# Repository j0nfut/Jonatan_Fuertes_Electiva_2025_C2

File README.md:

# Jonatan_Fuertes_Electiva_2025_C2
Repocitorio de electiva

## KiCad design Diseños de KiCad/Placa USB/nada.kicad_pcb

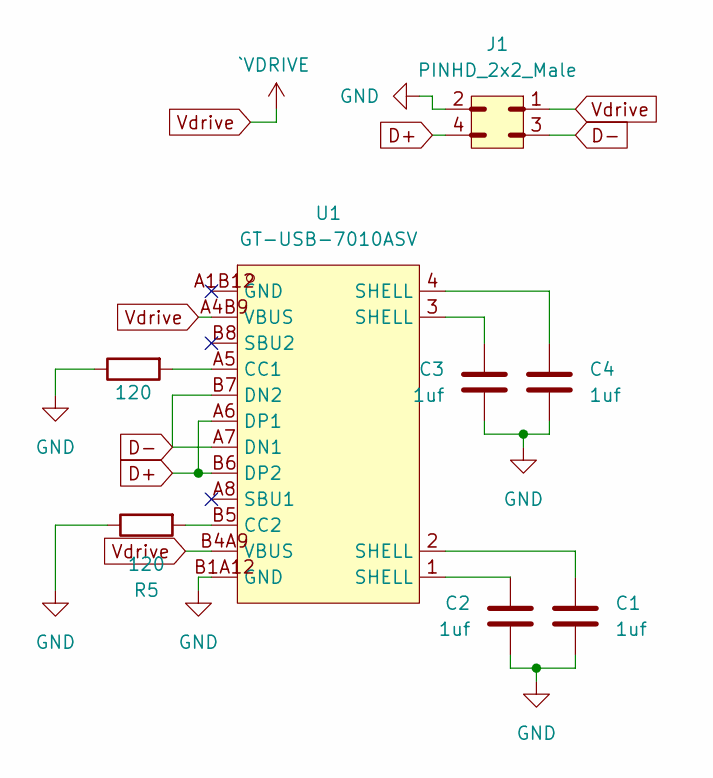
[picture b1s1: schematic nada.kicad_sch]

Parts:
C1, C2, C3, C4: 1uf; C_0603_1608Metric
J1: PINHD_2x2_Male; PinHeader_2x02_P2.54mm_Horizontal
R1, R5: 120; R_0603_1608Metric
U1: GT-USB-7010ASV; USB-C-SMDpersonalizado; LCSC Part C2988369

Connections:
D+: J1.4, U1.A6 (DP1), U1.B6 (DP2)
D-: J1.3, U1.A7 (DN1), U1.B7 (DN2)
GND: C1.2, C2.1, C3.1, C4.1, J1.2, R1.1, R5.1, U1.B1A12 (GND)
unnamed: C1.1, U1.2 (SHELL)
unnamed: C2.2, U1.1 (SHELL)
unnamed: C3.2, U1.3 (SHELL)
unnamed: C4.2, U1.4 (SHELL)
unnamed: R1.2, U1.A5 (CC1)
unnamed: R5.2, U1.B5 (CC2)
Vdrive: J1.1, U1.A4B9 (VBUS), U1.B4A9 (VBUS)

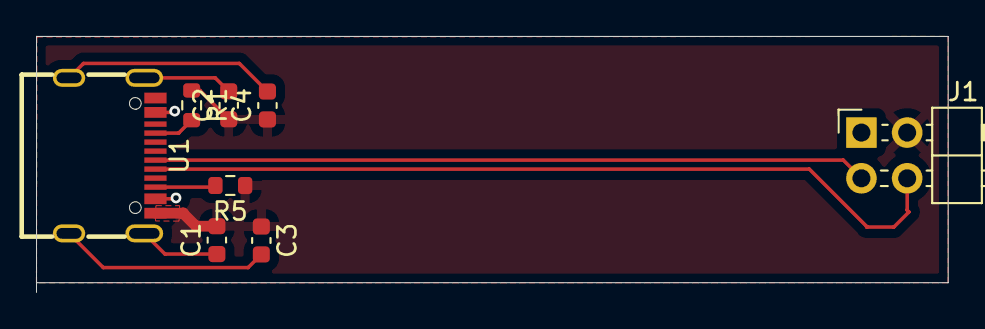
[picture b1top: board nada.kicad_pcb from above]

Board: 2 copper layers, 50.7 x 14.2 mm, 8 parts (0 on the bottom side), 10 nets.

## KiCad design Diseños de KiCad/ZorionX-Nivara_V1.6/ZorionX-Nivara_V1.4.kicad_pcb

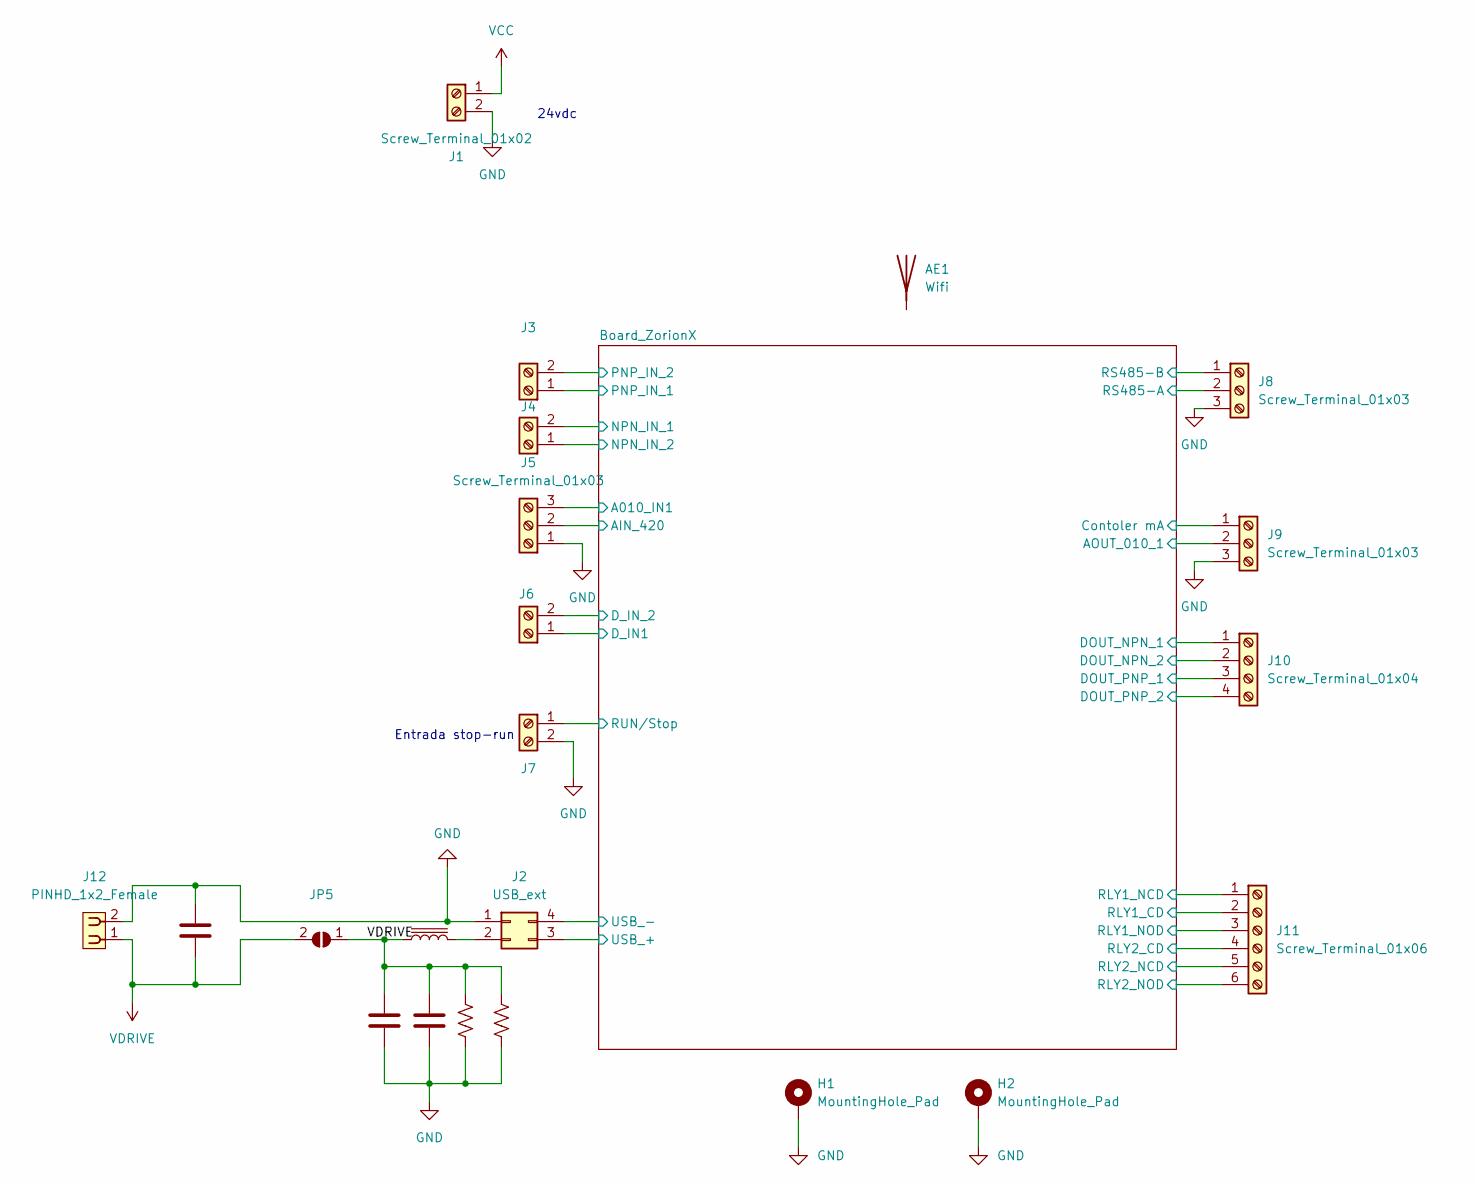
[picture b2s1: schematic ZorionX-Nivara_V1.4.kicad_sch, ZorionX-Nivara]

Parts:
AE1: Wifi
C18, C19, C20: 1uf; C_0603_1608Metric
H1, H2: MountingHole_Pad; MountingHole_3.2mm_M3_Pad_Via
J1, J3, J4, J6, J7: Screw_Terminal_01x02; TerminalBlock_Phoenix_PT-1,5-2-5.0-H_1x02_P5.00mm_Horizontal
J2: USB_ext; PinSocket_2x02_P2.54mm_Vertical
J5, J8, J9: Screw_Terminal_01x03; TerminalBlock_Phoenix_PT-1,5-3-3.5-H_1x03_P3.50mm_Horizontal
J10: Screw_Terminal_01x04; TerminalBlock_Phoenix_PT-1,5-4-5.0-H_1x04_P5.00mm_Horizontal
J11: Screw_Terminal_01x06; TerminalBlock_Phoenix_PT-1,5-6-5.0-H_1x06_P5.00mm_Horizontal
J12: PINHD_1x2_Female; PinSocket_1x02_P2.54mm_Vertical
JP5: SolderJumper_2_Open; SolderJumper-2_P1.3mm_Open_RoundedPad1.0x1.5mm
L2: L_Iron; L_Bourns-SRN6028
R25, R39: R_US; R_0603_1608Metric

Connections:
4_20v_mA: J5.2; also elsewhere on the board
/Board_ZorionX/A010_IN1: J5.3; also elsewhere on the board
/Board_ZorionX/AOUT_010_1: J9.2; also elsewhere on the board
/Board_ZorionX/Contoler mA: J9.1; also elsewhere on the board
/Board_ZorionX/DOUT_NPN_1: J10.1; also elsewhere on the board
/Board_ZorionX/DOUT_NPN_2: J10.2; also elsewhere on the board
/Board_ZorionX/DOUT_PNP_1: J10.3; also elsewhere on the board
/Board_ZorionX/DOUT_PNP_2: J10.4; also elsewhere on the board
/Board_ZorionX/D_IN1: J6.1; also elsewhere on the board
/Board_ZorionX/D_IN_2: J6.2; also elsewhere on the board
/Board_ZorionX/NPN_IN_1: J4.2; also elsewhere on the board
/Board_ZorionX/NPN_IN_2: J4.1; also elsewhere on the board
/Board_ZorionX/PNP_IN_1: J3.1; also elsewhere on the board
/Board_ZorionX/PNP_IN_2: J3.2; also elsewhere on the board
/Board_ZorionX/RLY1_CD: J11.2; also elsewhere on the board
/Board_ZorionX/RLY1_NCD: J11.1; also elsewhere on the board
/Board_ZorionX/RLY1_NOD: J11.3; also elsewhere on the board
/Board_ZorionX/RLY2_CD: J11.4; also elsewhere on the board
/Board_ZorionX/RLY2_NCD: J11.5; also elsewhere on the board
/Board_ZorionX/RLY2_NOD: J11.6; also elsewhere on the board
/Board_ZorionX/RS485-A: J8.2; also elsewhere on the board
/Board_ZorionX/RS485-B: J8.1; also elsewhere on the board
/Board_ZorionX/USB_+: J2.3; also elsewhere on the board
/Board_ZorionX/USB_-: J2.4; also elsewhere on the board
/RUN/Stop: J7.1
GND: C18.2, C19.2, C20.1, H1.1, H2.1, J1.2, J2.1, J5.1, J7.2, J8.3, J9.3, J12.2, R25.2, R39.2; also elsewhere on the board
unnamed: J2.2, L2.2
VCC: J1.1; also elsewhere on the board
VDRIVE: C18.1, C19.1, C20.2, J12.1, JP5.1 (A), JP5.2 (B), L2.1, R25.1, R39.1

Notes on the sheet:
24vdc
Entrada stop-run

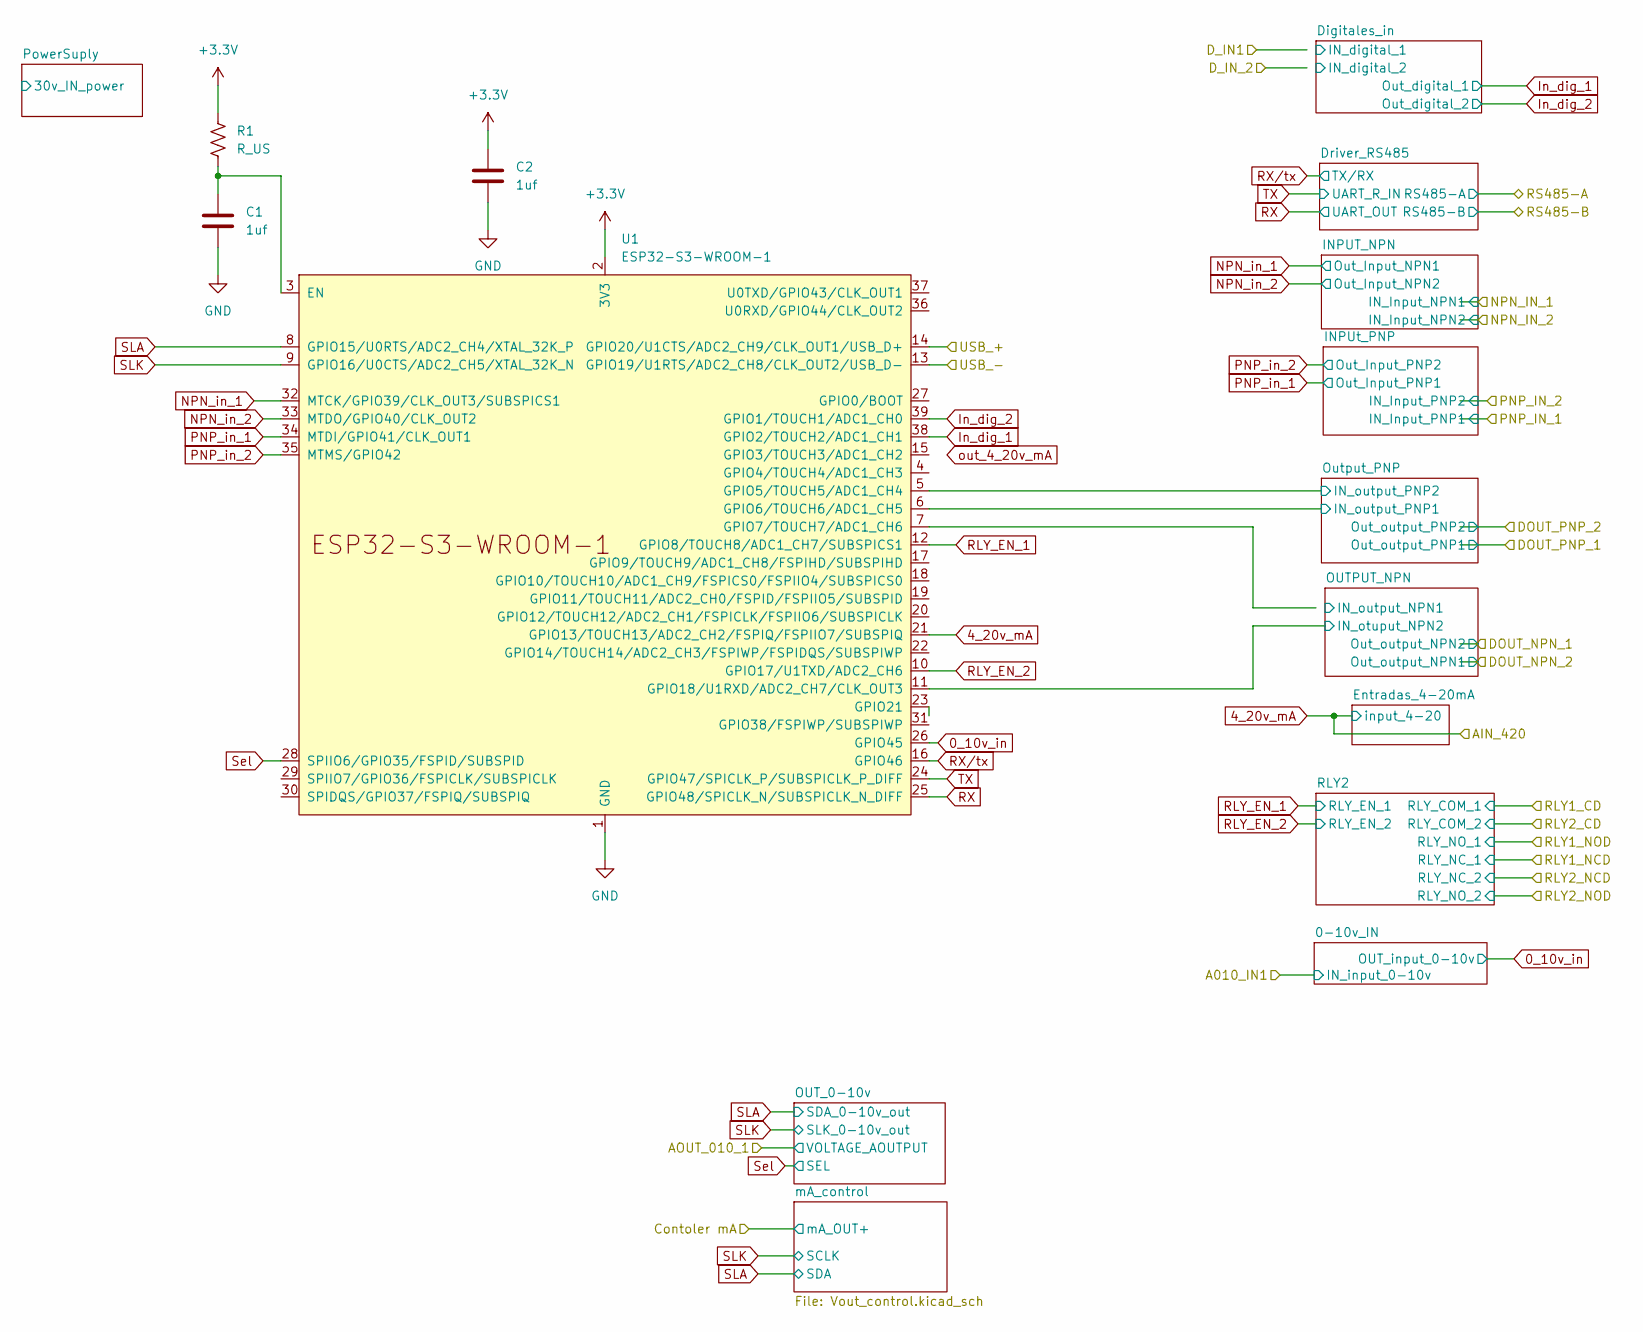
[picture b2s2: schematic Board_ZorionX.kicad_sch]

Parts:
C1, C2: 1uf; C_0603_1608Metric
R1: R_US; R_0603_1608Metric
U1: ESP32-S3-WROOM-1

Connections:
0_10v_in: U1.26 (GPIO45); also elsewhere on the board
4_20v_mA: U1.21 (GPIO13/TOUCH13/ADC2_CH2/FSPIQ/FSPIIO7/S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); also elsewhere on the board
+3.3V: C2.1, R1.1, U1.2 (3V3); also elsewhere on the board
/Board_ZorionX/OUTPUT_NPN/IN_otuput_NPN2: U1.11 (GPIO18/U1RXD/ADC2_CH7/CLK_OUT3); also elsewhere on the board
/Board_ZorionX/OUTPUT_NPN/IN_output_NPN1: U1.7 (GPIO7/TOUCH7/ADC1_CH6); also elsewhere on the board
/Board_ZorionX/Output_PNP/IN_output_PNP1: U1.6 (GPIO6/TOUCH6/ADC1_CH5); also elsewhere on the board
/Board_ZorionX/Output_PNP/IN_output_PNP2: U1.5 (GPIO5/TOUCH5/ADC1_CH4); also elsewhere on the board
/Board_ZorionX/USB_+: U1.14 (GPIO20/U1CTS/ADC2_CH9/CLK_OUT1/USB_D+); also elsewhere on the board
/Board_ZorionX/USB_-: U1.13 (GPIO19/U1RTS/ADC2_CH8/CLK_OUT2/USB_D-); also elsewhere on the board
GND: C1.2, C2.2, U1.1 (GND), U1.40 (GND), U1.41 (GND); also elsewhere on the board
In_dig_1: U1.38 (GPIO2/TOUCH2/ADC1_CH1); also elsewhere on the board
In_dig_2: U1.39 (GPIO1/TOUCH1/ADC1_CH0); also elsewhere on the board
NPN_in_1: U1.32 (MTCK/GPIO39/CLK_OUT3/SUBSPICS1); also elsewhere on the board
NPN_in_2: U1.33 (MTDO/GPIO40/CLK_OUT2); also elsewhere on the board
unnamed: C1.1, R1.2, U1.3 (EN)
PNP_in_1: U1.34 (MTDI/GPIO41/CLK_OUT1); also elsewhere on the board
PNP_in_2: U1.35 (MTMS/GPIO42); also elsewhere on the board
RLY_EN_1: U1.12 (GPIO8/TOUCH8/ADC1_CH7/SUBSPICS1); also elsewhere on the board
RLY_EN_2: U1.10 (GPIO17/U1TXD/ADC2_CH6); also elsewhere on the board
RX: U1.25 (GPIO48/SPICLK_N/SUBSPICLK_N_DIFF); also elsewhere on the board
RX/tx: U1.16 (GPIO46); also elsewhere on the board
SLA: U1.8 (GPIO15/U0RTS/ADC2_CH4/XTAL_32K_P); also elsewhere on the board
SLK: U1.9 (GPIO16/U0CTS/ADC2_CH5/XTAL_32K_N); also elsewhere on the board
Sel: U1.28 (SPIIO6/GPIO35/FSPID/SUBSPID); also elsewhere on the board
TX: U1.24 (GPIO47/SPICLK_P/SUBSPICLK_P_DIFF); also elsewhere on the board

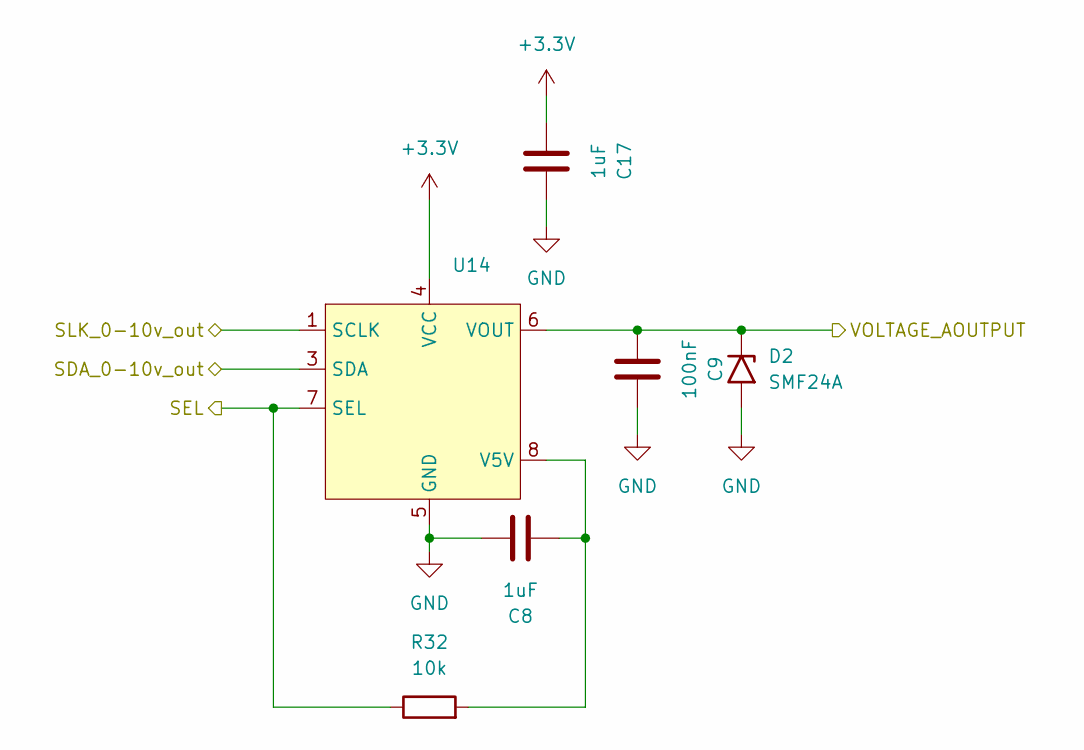
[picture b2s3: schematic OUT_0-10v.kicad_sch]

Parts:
C8, C17: 1uF; C_0603_1608Metric
C9: 100nF; C_0603_1608Metric
D2: SMF24A; D_SMF; LCSC# C7495269
R32: 10k; R_0603_1608Metric
U14: SOIC-8_5.3x6.2mm_P1.27mm

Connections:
+3.3V: C17.2, U14.4 (VCC); also elsewhere on the board
/Board_ZorionX/AOUT_010_1: C9.2, D2.1 (A1), U14.6 (VOUT); also elsewhere on the board
GND: C8.1, C9.1, C17.1, D2.2 (A2), U14.5 (GND); also elsewhere on the board
unnamed: C8.2, R32.2, U14.8 (V5V)
SLA: U14.3 (SDA); also elsewhere on the board
SLK: U14.1 (SCLK); also elsewhere on the board
Sel: R32.1, U14.7 (SEL); also elsewhere on the board

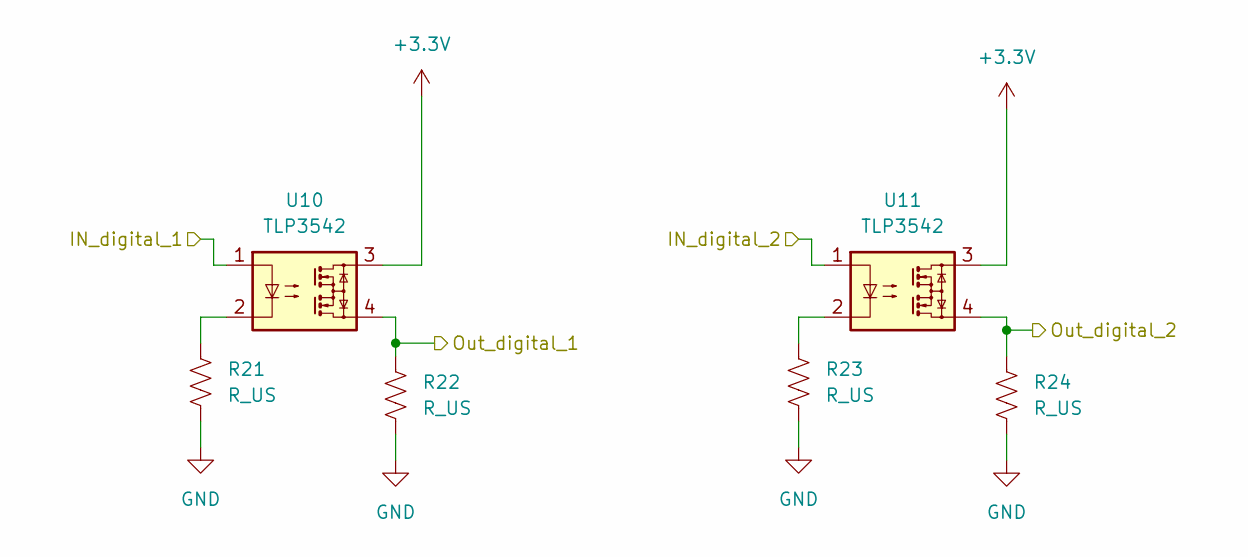
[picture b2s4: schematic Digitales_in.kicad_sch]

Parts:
R21, R22, R23, R24: R_US; R_0603_1608Metric
U10, U11: TLP3542; SOP-4_3.8x4.1mm_P2.54mm

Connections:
+3.3V: U10.3, U11.3; also elsewhere on the board
/Board_ZorionX/D_IN1: U10.1; also elsewhere on the board
/Board_ZorionX/D_IN_2: U11.1; also elsewhere on the board
GND: R21.2, R22.2, R23.2, R24.2; also elsewhere on the board
In_dig_1: R22.1, U10.4; also elsewhere on the board
In_dig_2: R24.1, U11.4; also elsewhere on the board
unnamed: R21.1, U10.2
unnamed: R23.1, U11.2

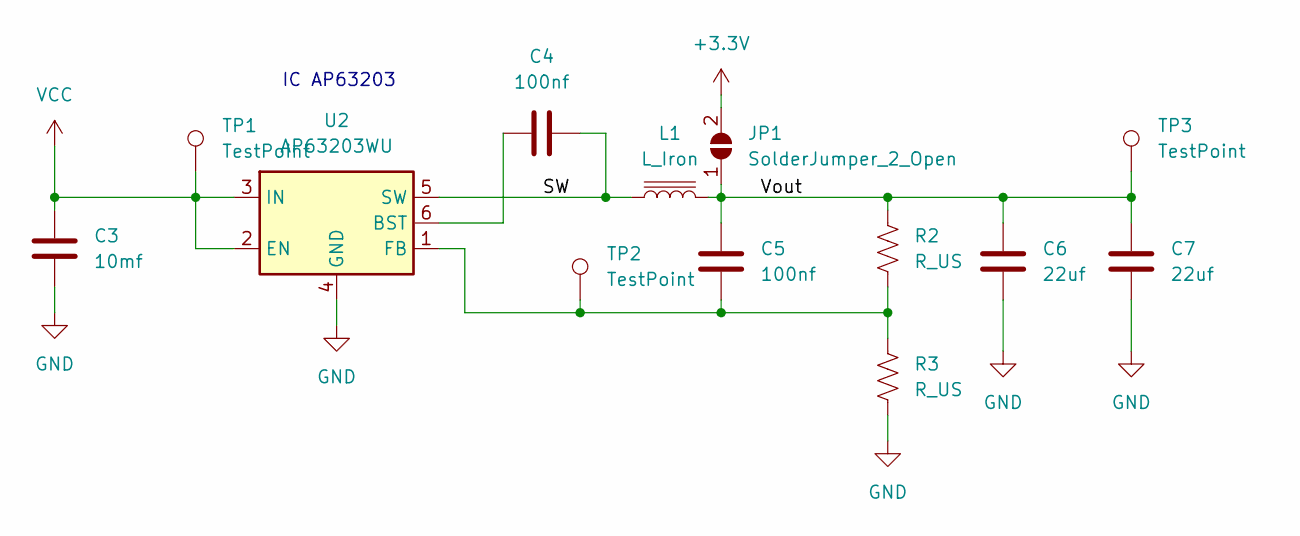
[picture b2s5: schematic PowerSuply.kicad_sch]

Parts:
C3: 10mf; C_1206_3216Metric
C4, C5: 100nf; C_0603_1608Metric
C6, C7: 22uf; C_0805_2012Metric
JP1: SolderJumper_2_Open; SolderJumper-2_P1.3mm_Open_RoundedPad1.0x1.5mm
L1: L_Iron; L_Bourns-SRN6028
R2, R3: R_US; R_0603_1608Metric
TP1, TP2, TP3: TestPoint; TestPoint_THTPad_1.0x1.0mm_Drill0.5mm
U2: AP63203WU; TSOT-23-6

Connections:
+3.3V: JP1.2 (B); also elsewhere on the board
/Board_ZorionX/PowerSuply/SW: C4.2, L1.1, U2.5 (SW)
/Board_ZorionX/PowerSuply/Vout: C5.1, C6.1, C7.1, JP1.1 (A), L1.2, R2.1, TP3.1
GND: C3.2, C6.2, C7.2, R3.2, U2.4 (GND); also elsewhere on the board
unnamed: C4.1, U2.6 (BST)
unnamed: C5.2, R2.2, R3.1, TP2.1, U2.1 (FB)
VCC: C3.1, TP1.1, U2.2 (EN), U2.3 (IN); also elsewhere on the board

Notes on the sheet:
IC AP63203

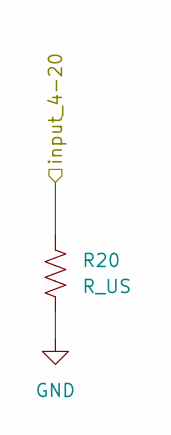
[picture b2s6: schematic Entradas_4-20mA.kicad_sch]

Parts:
R20: R_US; R_0603_1608Metric

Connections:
4_20v_mA: R20.1; also elsewhere on the board
GND: R20.2; also elsewhere on the board

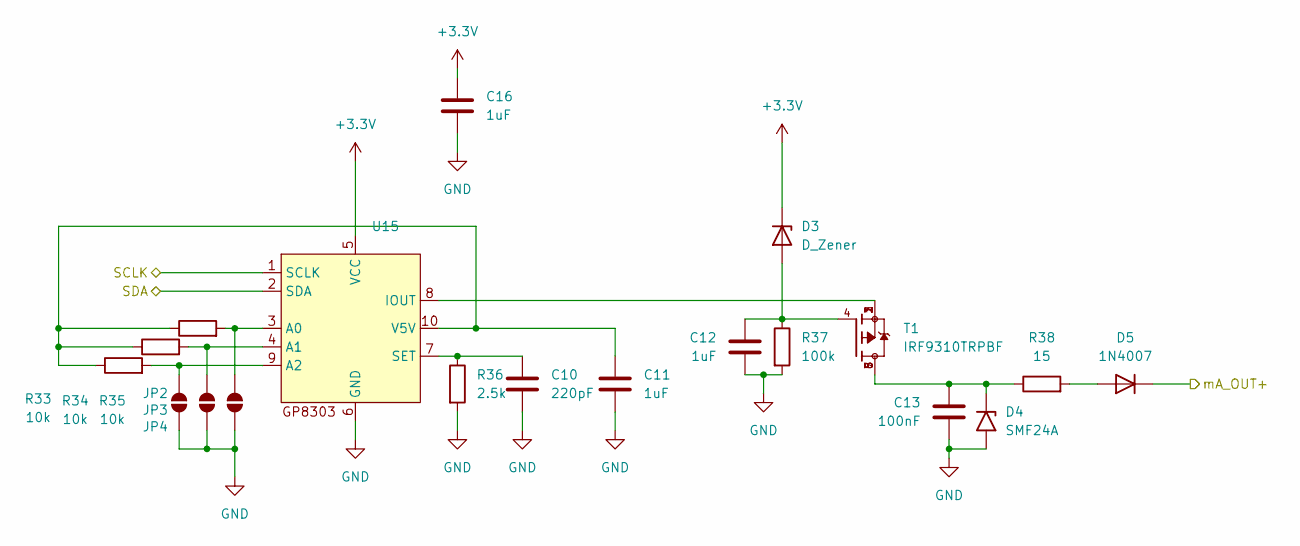
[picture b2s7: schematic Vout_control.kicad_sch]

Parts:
C10: 220pF; C_0603_1608Metric
C11, C12, C16: 1uF; C_0603_1608Metric
C13: 100nF; C_0603_1608Metric
D3: D_Zener; D_SMF
D4: SMF24A; D_SMF
D5: 1N4007; D_DO-41_SOD81_P10.16mm_Horizontal
JP2, JP3, JP4: SolderJumper_2_Open; SolderJumper-2_P1.3mm_Open_RoundedPad1.0x1.5mm
R33, R34, R35: 10k; R_0603_1608Metric
R36: 2.5k; R_0603_1608Metric
R37: 100k; R_0603_1608Metric
R38: 15; R_0603_1608Metric
T1: IRF9310TRPBF; SO-8_3.9x4.9mm_P1.27mm
U15: SSOP-10-1EP_3.9x4.9mm_P1mm_EP2.1x3.3mm

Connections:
+3.3V: C16.1, D3.1 (K), U15.5 (VCC); also elsewhere on the board
/Board_ZorionX/Contoler mA: D5.1 (K); also elsewhere on the board
GND: C10.2, C11.2, C12.2, C13.2, C16.2, D4.2 (A2), JP2.1 (A), JP3.1 (A), JP4.1 (A), R36.2, R37.2, U15.6 (GND); also elsewhere on the board
unnamed: C12.1, D3.2 (A), R37.1, T1.4
unnamed: C13.1, D4.1 (A1), R38.1, T1.5, T1.6, T1.7, T1.8
unnamed: D5.2 (A), R38.2
unnamed: JP2.2 (B), R33.2, U15.9 (A2)
unnamed: JP3.2 (B), R34.2, U15.4 (A1)
unnamed: JP4.2 (B), R35.2, U15.3 (A0)
unnamed: T1.1, T1.2, T1.3, U15.8 (IOUT)
unnamed: C10.1, R36.1, U15.7 (SET)
unnamed: C11.1, R33.1, R34.1, R35.1, U15.10 (V5V)
SLA: U15.2 (SDA); also elsewhere on the board
SLK: U15.1 (SCLK); also elsewhere on the board

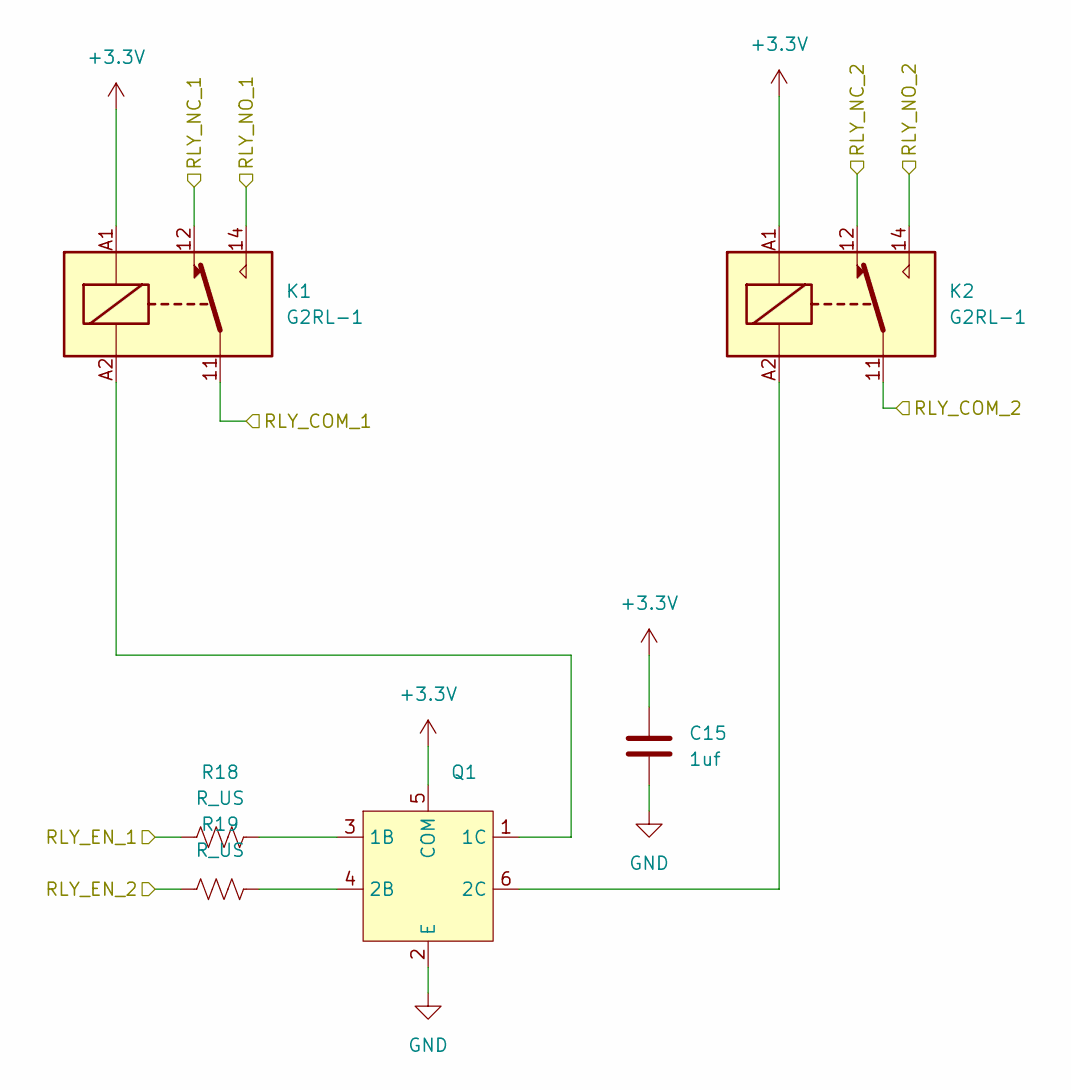
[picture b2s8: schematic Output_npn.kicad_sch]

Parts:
C15: 1uf; C_0603_1608Metric
K1, K2: G2RL-1; Relay_SPDT_Omron_G2RL-1
Q1: TSOT-23-6; LCSC# C2984831
R18, R19: R_US; R_0603_1608Metric

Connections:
+3.3V: C15.1, K1.A1, K2.A1, Q1.5 (COM); also elsewhere on the board
/Board_ZorionX/RLY1_CD: K1.11; also elsewhere on the board
/Board_ZorionX/RLY1_NCD: K1.12; also elsewhere on the board
/Board_ZorionX/RLY1_NOD: K1.14; also elsewhere on the board
/Board_ZorionX/RLY2_CD: K2.11; also elsewhere on the board
/Board_ZorionX/RLY2_NCD: K2.12; also elsewhere on the board
/Board_ZorionX/RLY2_NOD: K2.14; also elsewhere on the board
GND: C15.2, Q1.2 (E); also elsewhere on the board
unnamed: Q1.3 (1B), R18.2
unnamed: K1.A2, Q1.1 (1C)
unnamed: Q1.4 (2B), R19.2
unnamed: K2.A2, Q1.6 (2C)
RLY_EN_1: R18.1; also elsewhere on the board
RLY_EN_2: R19.1; also elsewhere on the board

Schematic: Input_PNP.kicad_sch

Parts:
R6, R7, R8, R9: R_US; R_0603_1608Metric
U4, U5: TLP3542; SOP-4_3.8x4.1mm_P2.54mm

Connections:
+3.3V: R7.1, R9.1; also elsewhere on the board
/Board_ZorionX/DOUT_NPN_1: R9.2, U5.3; also elsewhere on the board
/Board_ZorionX/DOUT_NPN_2: R7.2, U4.3; also elsewhere on the board
/Board_ZorionX/OUTPUT_NPN/IN_otuput_NPN2: U5.1; also elsewhere on the board
/Board_ZorionX/OUTPUT_NPN/IN_output_NPN1: U4.1; also elsewhere on the board
GND: R6.2, R8.2, U4.4, U5.4; also elsewhere on the board
unnamed: R6.1, U4.2
unnamed: R8.1, U5.2

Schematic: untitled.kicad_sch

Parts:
R26, R27, R28, R29: R_US; R_0603_1608Metric
U12, U13: TLP3542; SOP-4_3.8x4.1mm_P2.54mm

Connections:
+3.3V: R27.1, R29.1; also elsewhere on the board
/Board_ZorionX/NPN_IN_1: U12.1; also elsewhere on the board
/Board_ZorionX/NPN_IN_2: U13.1; also elsewhere on the board
GND: R26.2, R28.2, U12.4, U13.4; also elsewhere on the board
NPN_in_1: R27.2, U12.3; also elsewhere on the board
NPN_in_2: R29.2, U13.3; also elsewhere on the board
unnamed: R26.1, U12.2
unnamed: R28.1, U13.2

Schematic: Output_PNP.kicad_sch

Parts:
R10, R11, R12, R13: R_US; R_0603_1608Metric
U6, U7: TLP3542; SOP-4_3.8x4.1mm_P2.54mm

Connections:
+3.3V: U6.3, U7.3; also elsewhere on the board
/Board_ZorionX/DOUT_PNP_1: R11.1, U6.4; also elsewhere on the board
/Board_ZorionX/DOUT_PNP_2: R13.1, U7.4; also elsewhere on the board
/Board_ZorionX/Output_PNP/IN_output_PNP1: U6.1; also elsewhere on the board
/Board_ZorionX/Output_PNP/IN_output_PNP2: U7.1; also elsewhere on the board
GND: R10.2, R11.2, R12.2, R13.2; also elsewhere on the board
unnamed: R10.1, U6.2
unnamed: R12.1, U7.2

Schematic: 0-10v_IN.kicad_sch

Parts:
R30, R31: R_US; R_0603_1608Metric

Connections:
0_10v_in: R30.2, R31.1; also elsewhere on the board
/Board_ZorionX/A010_IN1: R30.1; also elsewhere on the board
GND: R31.2; also elsewhere on the board

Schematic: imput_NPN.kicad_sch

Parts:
R14, R15, R16, R17: R_US; R_0603_1608Metric
U8, U9: TLP3542; SOP-4_3.8x4.1mm_P2.54mm

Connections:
+3.3V: U8.3, U9.3; also elsewhere on the board
/Board_ZorionX/PNP_IN_1: U8.1; also elsewhere on the board
/Board_ZorionX/PNP_IN_2: U9.1; also elsewhere on the board
GND: R14.2, R15.2, R16.2, R17.2; also elsewhere on the board
unnamed: R14.1, U8.2
unnamed: R16.1, U9.2
PNP_in_1: R15.1, U8.4; also elsewhere on the board
PNP_in_2: R17.1, U9.4; also elsewhere on the board

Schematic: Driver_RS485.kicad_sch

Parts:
C14: 1uf; C_0603_1608Metric
D1: SM712_SOT23; SOT-23
R4, R5: 120; R_0603_1608Metric
U3: Rs_485

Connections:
+3.3V: C14.1, U3.1 (VCC); also elsewhere on the board
/Board_ZorionX/RS485-A: D1.1 (A1), R5.2; also elsewhere on the board
/Board_ZorionX/RS485-B: D1.2 (A2), R4.2; also elsewhere on the board
GND: C14.2, D1.3 (common), U3.2 (GND); also elsewhere on the board
unnamed: R5.1, U3.9 (A)
unnamed: R4.1, U3.8 (B)
RX: U3.4 (RXD); also elsewhere on the board
RX/tx: U3.5 (CON); also elsewhere on the board
TX: U3.3 (TXD); also elsewhere on the board

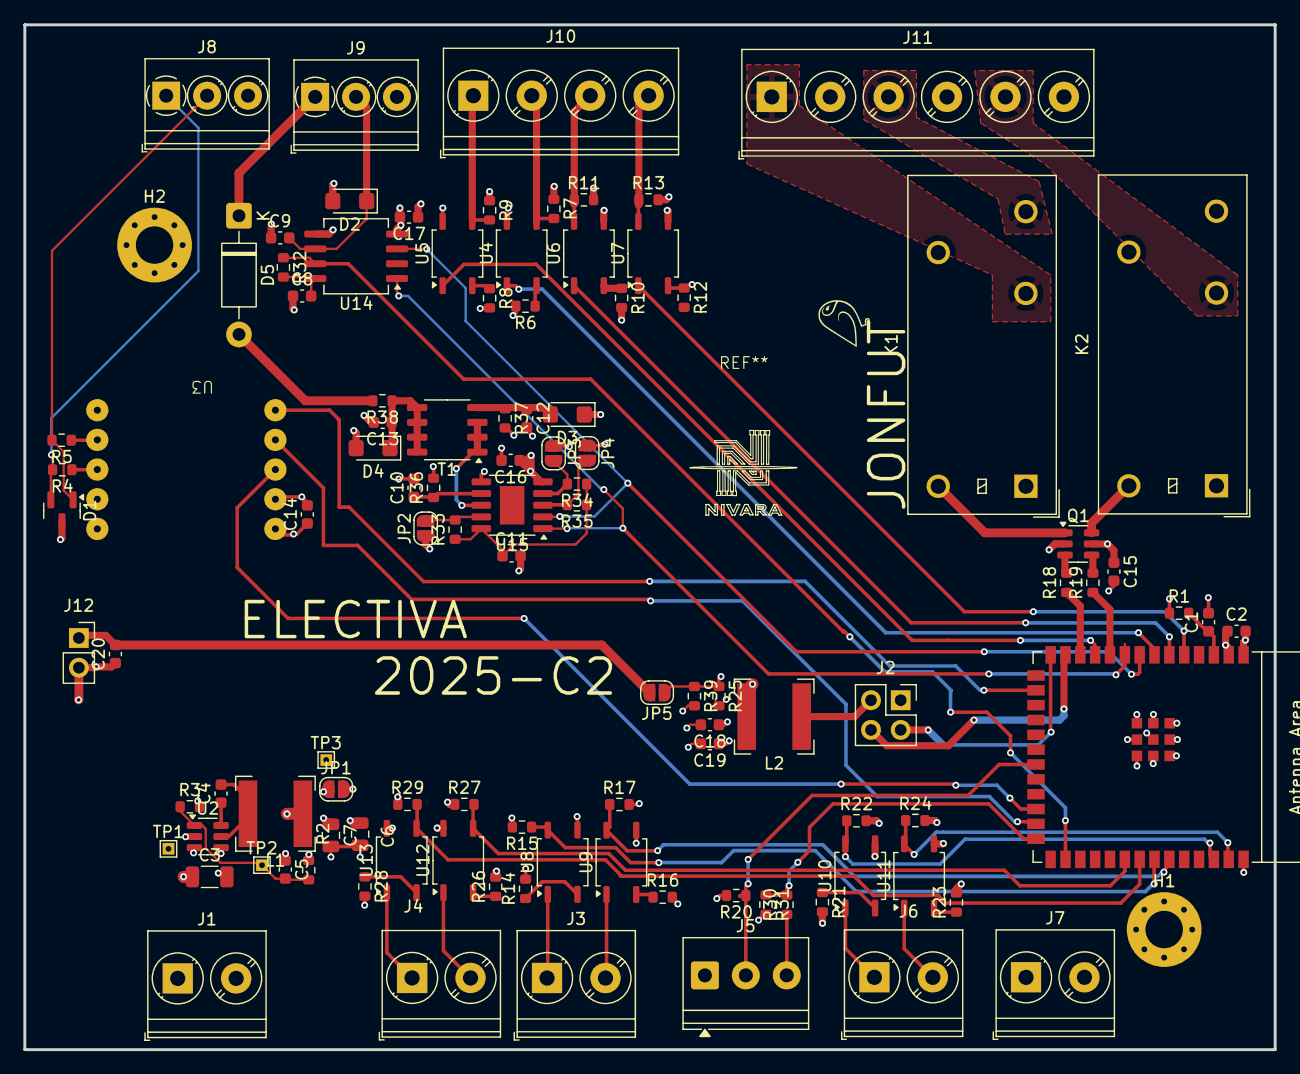
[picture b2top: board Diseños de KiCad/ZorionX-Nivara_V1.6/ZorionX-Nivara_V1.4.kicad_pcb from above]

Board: 4 copper layers, 107.0 x 87.7 mm, 107 parts (0 on the bottom side), 79 nets.

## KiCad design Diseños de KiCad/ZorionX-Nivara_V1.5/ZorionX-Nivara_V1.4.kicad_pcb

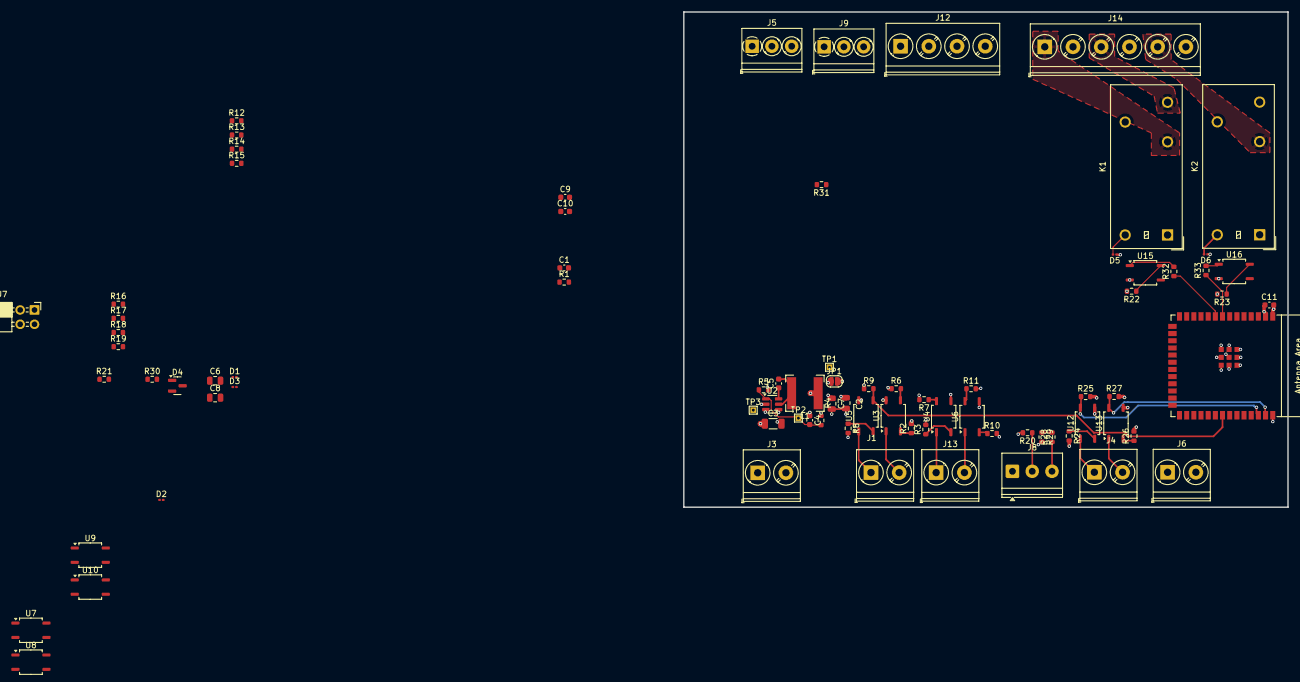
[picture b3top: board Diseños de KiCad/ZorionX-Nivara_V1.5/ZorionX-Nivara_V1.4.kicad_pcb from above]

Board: 4 copper layers, 107.0 x 87.7 mm, 82 parts (0 on the bottom side), 58 nets.

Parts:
C1, C9, C10, C11: 1uf; C_0603_1608Metric
C2, C7: 22uf; C_0805_2012Metric
C3: 10mf; C_1206_3216Metric
C4, C5: 100nf; C_0603_1608Metric
C6: 0.1uf; C_0805_2012Metric
C8: 1uf; C_0805_2012Metric
D1: D_Zener; L_0201_0603Metric
D2, D3, D5, D6: D; L_0201_0603Metric
D4: SM712_SOT23; SOT-23
J1, J3, J4, J6, J13: Screw_Terminal_01x02; TerminalBlock_Phoenix_PT-1,5-2-5.0-H_1x02_P5.00mm_Horizontal
J5, J8, J9: Screw_Terminal_01x03; TerminalBlock_Phoenix_PT-1,5-3-3.5-H_1x03_P3.50mm_Horizontal
J7: USB_ext; PinSocket_2x02_P2.54mm_Horizontal
J12: Screw_Terminal_01x04; TerminalBlock_Phoenix_PT-1,5-4-5.0-H_1x04_P5.00mm_Horizontal
J14: Screw_Terminal_01x06; TerminalBlock_Phoenix_PT-1,5-6-5.0-H_1x06_P5.00mm_Horizontal
JP1: SolderJumper_2_Open; SolderJumper-2_P1.3mm_Open_RoundedPad1.0x1.5mm
K1, K2: G2RL-1; Relay_SPDT_Omron_G2RL-1
L1: L_Iron; L_Bourns-SRN6028
R1, R2, R3, R4, R5, R6, R7, R8, R9, R10, R11, R12, R13, R14, R15, R16, R17, R18, R19, R20, R21, R22, R23, R24, R25, R26, R27, R28, R29, R30, R31, R32, R33: R_US; R_0603_1608Metric
TP1, TP2, TP3: TestPoint; TestPoint_THTPad_1.0x1.0mm_Drill0.5mm
U1: ESP32-S3-WROOM-1
U2: AP63203WU; TSOT-23-6
U3, U4, U5, U6, U7, U8, U9, U10, U12, U13, U15, U16: TLP3542; SOP-4_3.8x4.1mm_P2.54mm

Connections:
0_10v_in: R28.2, R29.1
4_20v_mA: J8.2, R20.1
+3.3V: C9.2, C10.2, C11.1, D2.1 (K), D5.1 (K), D6.1 (K), J12.1, J12.2, JP1.2 (B), K1.A1, K2.A1, R1.1, R6.1, R9.1, R17.1, R19.1, U1.2 (3V3), U4.3, U6.3, U7.3, U8.3, U12.3, U13.3
/Board_ZorionX/AOUT_010_1: C6.1, D1.1 (K), D2.2 (A), D3.1 (K), J9.2
/Board_ZorionX/DOUT_PNP_1: J12.3, R13.1, U7.4
/Board_ZorionX/DOUT_PNP_2: J12.4, R15.1, U8.4
/Board_ZorionX/D_IN1: J4.1, U12.1
/Board_ZorionX/D_IN_2: J4.2, U13.1
/Board_ZorionX/INPUt_PNP/Out_Input_PNP1: R7.1, U4.4
/Board_ZorionX/INPUt_PNP/Out_Input_PNP2: R11.1, U6.4
/Board_ZorionX/NPN_IN_2: J1.1, U5.1
/Board_ZorionX/OUTPUT_NPN/IN_otuput_NPN2: U1.11 (GPIO18/U1RXD/ADC2_CH7/CLK_OUT3), U10.1
/Board_ZorionX/OUTPUT_NPN/IN_output_NPN1: U1.7 (GPIO7/TOUCH7/ADC1_CH6), U9.1
/Board_ZorionX/Output_PNP/IN_output_PNP1: U1.6 (GPIO6/TOUCH6/ADC1_CH5), U7.1
/Board_ZorionX/Output_PNP/IN_output_PNP2: U1.5 (GPIO5/TOUCH5/ADC1_CH4), U8.1
/Board_ZorionX/PNP_IN_2: J13.1, U4.1
/Board_ZorionX/PowerSuply/SW: C5.2, L1.1, U2.5 (SW)
/Board_ZorionX/PowerSuply/Vout: C2.1, C4.1, C7.1, JP1.1 (A), L1.2, R4.1, TP1.1
/Board_ZorionX/RLY1_CD: J14.2, K1.11
/Board_ZorionX/RLY1_NCD: J14.1, K1.12
/Board_ZorionX/RLY1_NOD: J14.3, K1.14
/Board_ZorionX/RLY2_CD: J14.4, K2.11
/Board_ZorionX/RLY2_NCD: J14.5, K2.12
/Board_ZorionX/RLY2_NOD: J14.6, K2.14
/Board_ZorionX/RS485-A: D4.1 (A1), J5.2, R30.2
/Board_ZorionX/RS485-B: D4.2 (A2), J5.1, R31.2
/Board_ZorionX/USB_+: J7.4, U1.14 (GPIO20/U1CTS/ADC2_CH9/CLK_OUT1/USB_D+)
/Board_ZorionX/USB_-: J7.3, U1.13 (GPIO19/U1RTS/ADC2_CH8/CLK_OUT2/USB_D-)
GND: C1.2, C2.2, C3.2, C6.2, C7.2, C8.2, C11.2, D1.2 (A), D3.2 (A), D4.3 (common), J3.2, J5.3, J6.2, J7.2, J8.1, J9.3, R2.2, R3.2, R5.2, R7.2, R8.2, R10.2, R11.2, R12.2, R13.2, R14.2, R15.2, R16.2, R18.2, R20.2, R21.2, R22.2, R23.2, R24.2, R25.2, R26.2, R27.2, R29.2, U1.1 (GND), U1.40 (GND), U1.41 (GND), U2.4 (GND), U3.4, U5.4, U9.4, U10.4, U15.2, U16.2
In_dig_1: R25.1, U1.38 (GPIO2/TOUCH2/ADC1_CH1), U12.4
In_dig_2: R27.1, U1.39 (GPIO1/TOUCH1/ADC1_CH0), U13.4
NPN_in_1: J1.2, R6.2, U1.32 (MTCK/GPIO39/CLK_OUT3/SUBSPICS1), U3.1, U3.3
NPN_in_2: R9.2, U1.33 (MTDO/GPIO40/CLK_OUT2), U5.3
unnamed: D5.2 (A), K1.A2
unnamed: D6.2 (A), K2.A2
unnamed: R2.1, U3.2
unnamed: R3.1, U4.2
unnamed: R8.1, U5.2
unnamed: R10.1, U6.2
unnamed: R12.1, U7.2
unnamed: R14.1, U8.2
unnamed: R16.1, U9.2
unnamed: R17.2, U9.3
unnamed: R18.1, U10.2
unnamed: R19.2, U10.3
unnamed: R22.1, U15.4
unnamed: R23.1, U16.4
unnamed: R24.1, U12.2
unnamed: R26.1, U13.2
unnamed: R32.2, U15.1
unnamed: R33.2, U16.1
unnamed: C1.1, R1.2, U1.3 (EN)
unnamed: C5.1, U2.6 (BST)
unnamed: C4.2, R4.2, R5.1, TP2.1, U2.1 (FB)
PNP_in_1: J13.2, U1.34 (MTDI/GPIO41/CLK_OUT1), U1.35 (MTMS/GPIO42), U6.1
RLY_EN_1: R33.1, U1.8 (GPIO15/U0RTS/ADC2_CH4/XTAL_32K_P)
RLY_EN_2: R32.1, U1.9 (GPIO16/U0CTS/ADC2_CH5/XTAL_32K_N)
VCC: C3.1, J3.1, TP3.1, U2.2 (EN), U2.3 (IN)

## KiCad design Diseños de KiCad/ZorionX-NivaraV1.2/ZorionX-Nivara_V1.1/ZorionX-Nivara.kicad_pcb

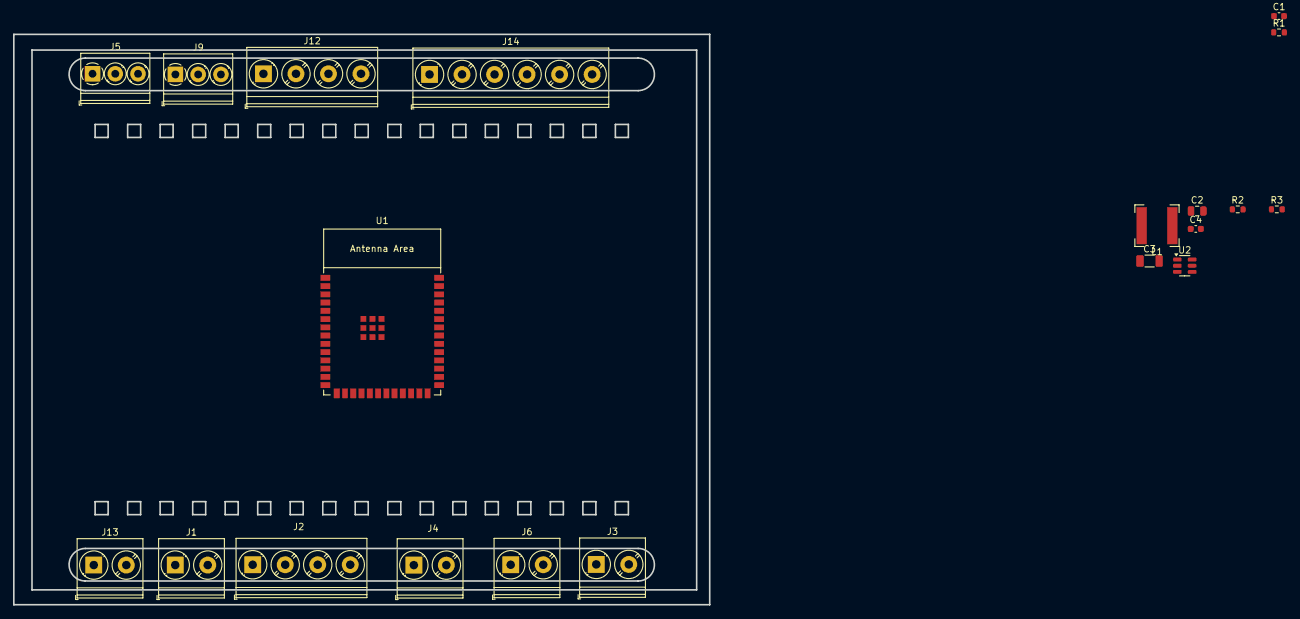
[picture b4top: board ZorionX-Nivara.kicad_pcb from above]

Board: 2 copper layers, 107.0 x 87.7 mm, 20 parts (0 on the bottom side), 3 nets, no tracks yet.

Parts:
C1: 1uf; C_0603_1608Metric
C2: 22uf; C_0805_2012Metric
C3: 10mf; C_1206_3216Metric
C4: 100nf; C_0603_1608Metric
J1, J3, J4, J6, J13: Screw_Terminal_01x02; TerminalBlock_Phoenix_PT-1,5-2-5.0-H_1x02_P5.00mm_Horizontal
J2, J12: Screw_Terminal_01x04; TerminalBlock_Phoenix_PT-1,5-4-5.0-H_1x04_P5.00mm_Horizontal
J5, J9: Screw_Terminal_01x03; TerminalBlock_Phoenix_PT-1,5-3-3.5-H_1x03_P3.50mm_Horizontal
J14: Screw_Terminal_01x06; TerminalBlock_Phoenix_PT-1,5-6-5.0-H_1x06_P5.00mm_Horizontal
L1: L_Iron; L_Bourns-SRN6028
R1, R2, R3: R_US; R_0603_1608Metric
U1: ESP32-S3-WROOM-1
U2: AP63203WU; TSOT-23-6

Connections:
+3.3V: R1.1, U1.2 (3V3)
GND: C1.2, J2.4, J3.2, J5.3, J6.2, J9.3, U1.1 (GND), U1.40 (GND), U1.41 (GND)
unnamed: C1.1, R1.2, U1.3 (EN)

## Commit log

2025-05-30 Create Resumenes_Investigaciones
2025-08-20 Add files via upload
    eso ta de to
2025-08-20 Tráteme bien
